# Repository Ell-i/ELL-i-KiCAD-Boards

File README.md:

# ELL-i-KiCAD-Boards
ELL-i's Public KiCAD Designs

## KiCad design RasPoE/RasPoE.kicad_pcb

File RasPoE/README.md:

#RasPoE user instructions
##Caution

Always disconnect cable between RasPoE and Rasberry Pi before connecting or disconnecting cable between RasPoE and PoE switch to avoid damage to your Raspberry Pi!

##Usage
Setting up RasPoE is simple: you need a Power over Ethernet (PoE) switch or injector to provide power to your Raspberry Pi. Mount RasPoE on top of your Raspberry Pi, connect RasPoE to PoE switch and finally connect RasPoE to Raspberry Pi. No special software is needed, start-up is automatic.

If you disconnect the RasPoE, always disconnect the cable to Raspberry Pi first! The PoE voltages can jump over transformer when cable is disconnected, disconnecting cable to Raspberry Pi prevents damage.

RasPoE uses only 5V and GND pins and it has tall header, which means you can stack Raspberry Pi HAT on top of it.
Specification

RasPoE is based on AG9805-M PoE DC/DC module which automatically negotiates the PoE power and provides 5V DC for Raspberry Pi.

While AG9805M can provide 1.8 A (9W) of power, current to Raspberry Pi is limited by 1.25 A self-resettible fuse. Please note the total current if you are using power-hungry USB peripherals

##Open Hardware
RasPoE is open source hardware, you can download the design files at ELL-i Open Source Co-operative's github-repository here. You can find out more about ELL-i at [ELL-i's website](http://ell-i.org).

##Hacking
RasPoE is made for hackers and makers. We cannot guess every possible application where RasPoE will be used so we have made things simple for some modifications.

###Raw PoE power
If your project needs unregulated high voltage, you can tap into RasPoE's "Raw PoE" pads. These pads expose the PoE voltage for your convenience, you can solder wires to them. Please note that any load on these pads will disrupt the PoE negotiation, so you must use relay controlled by Raspberry Pi to connect high voltage load only after the power has been setup. Do not add a lot of capacitance on these pins either to avoid inrush current tripping your PoE switch overcurrent protection.

###DC output pins
If you need to power some small external load, such as Arduino, you can add connector to the "DC OUT" pins. This output is not protected by fuse, so please be careful to not overload the AG9805 to avoid damage to your RasPoE.
Adjust

If you need to tune the output voltage a bit, you can solder a resistor to ADJUST pin as instructed in [AG9805-M datasheet](http://www.semiconductorstore.com/pages/asp/DownloadAttachment.asp?d=83464&e=i). Please be careful to not exceed your Raspberry Pi's maximum voltage.

###Other voltages

AG9803 and AG98012 modules provide 3.3 V and 12 V outputs respectively. You can desolder the AG9805 using hot air, disconnect the fuse F1 and solder a replacement module in if you want to! This is perfect for Raspberry Pi HATs which require 12V and provide 5V to RaspBerry Pi.

##Troubleshooting

If your Raspberry Pi does not power up or network connection fails, please check:

    Are you using a CAT5 or better Ethernet cable?
    Is the RasPoE properly connected?
    Does your switch support PoE technology?

If the problem remains, please contact us at support@ell-i.org and we'll help you with the issue. 

RasPoE emits high-pitched noise when there is  low load, this is normal. You can add optional load resistors R6, R7 to avoid this noise.

##How to buy
RasPoE is available through [Elecrow's webshop](http://www.elecrow.com/raspoeraspberry-pi-poe-shield-p-1479.html).

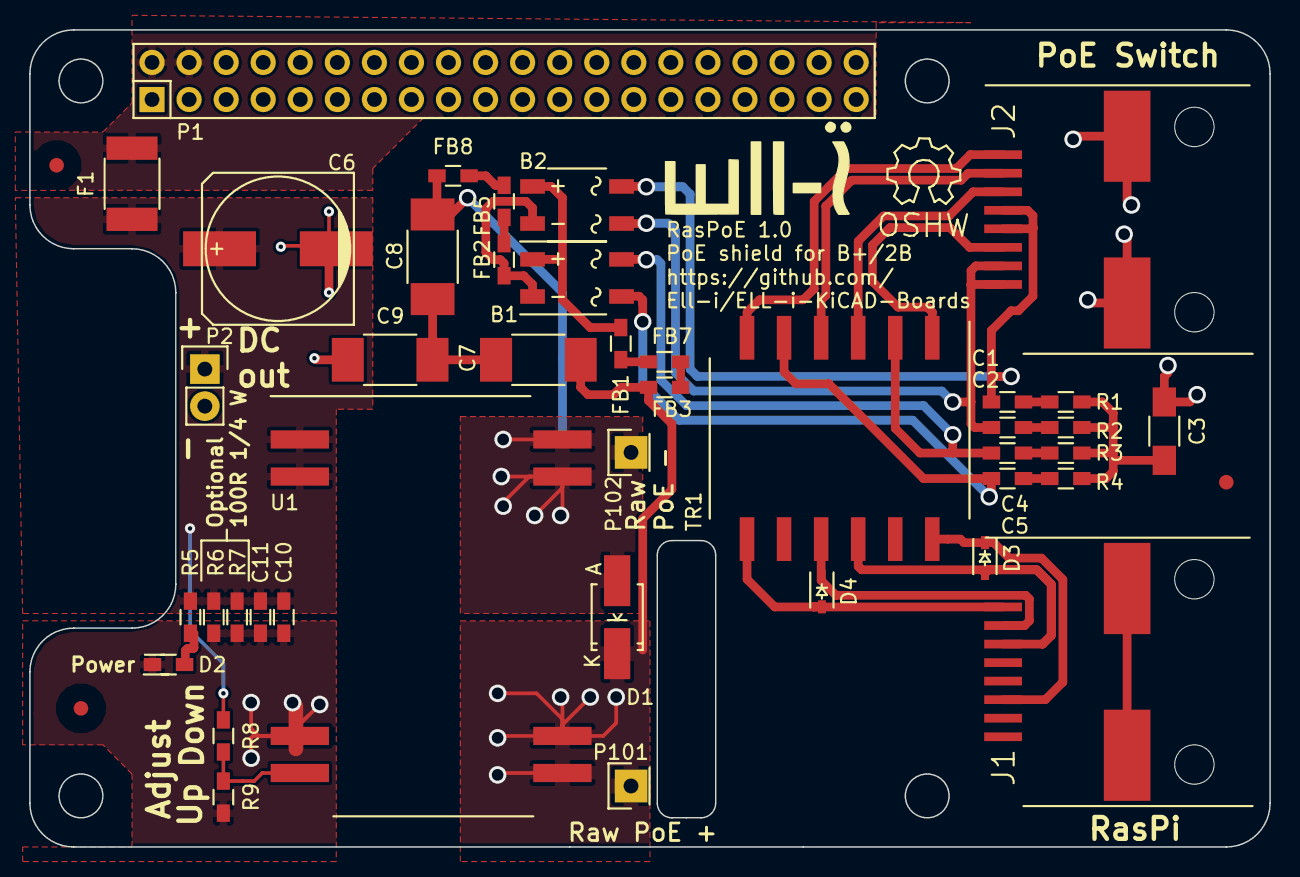
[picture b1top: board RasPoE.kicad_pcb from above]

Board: 2 copper layers, 85.0 x 56.0 mm, 46 parts (0 on the bottom side), 32 nets.

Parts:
B1, B2: MB110S; TO-269AA
C1, C2, C4, C5: 10n 100V; R_0603_HandSoldering
C3: 1n 2kV; C_1206_HandSoldering
C6: 470u; c_elec_10x10
C7, C8, C9: 4n7 2kV; C_1812_HandSoldering
C10: 100n; R_0603_HandSoldering
C11: 10u; R_0603_HandSoldering
D1: SMA58; Diode-SMA_Handsoldering
D2: LED; R_0603_HandSoldering
D3, D4: TVS; SOD-323
F1: PTC 1A25; R_1812
FB1, FB2, FB3, FB5, FB7, FB8: WE 742792651; R_0603_HandSoldering
FID1, FID2, FID3: 1, 2 mm; Fiducial_2mm_dia
J1: RJSSE-5080; RJSSE-5380
J2: RJSSE-5380
LOGO101: OPEN_HARDWARE_1; Symbol_OSHW-Logo_SilkScreen
LOGO102: ELL-i; ELL-i_large
P1: CONN_02X20; Pin_Header_Straight_2x20
P2: Screw terminal 2.54mm; Pin_Header_Straight_1x02
P101, P102: Wire pad; Pin_Header_Straight_1x01
R1, R2, R3, R4: 75R; R_0603_HandSoldering
R5: 180R; R_0603_HandSoldering
R6, R7: 100R 250 mW; R_0603_HandSoldering
R8, R9: R; R_0603_HandSoldering
TR1: WE_749012011
U1: AG9805-MT; AG9800

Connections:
+5V: F1.2, P1.2, P1.4
/ADJ: R8.2, R9.1, U1.4
/AG_IN_+: C7.1, D1.1, FB7.2, P101.1, U1.5, U1.6
/AG_IN_-: C8.1, D1.2, FB8.2, P102.1, U1.7, U1.8
/AG_OUT_+: C6.1, C10.1, C11.1, F1.1, P2.1, R5.1, R6.1, R7.1, R8.1, U1.1, U1.2
/POE_A+: B1.4, C4.1, TR1.2
/POE_A-: B1.2, C5.1, TR1.5
/POE_B+: B2.2, C2.1, J2.7, J2.8
/POE_B-: B2.4, C1.1, J2.4, J2.5
/RD+: D3.2, J1.3, TR1.10
/RD-: D3.1, J1.6, TR1.12
/RX+: J2.3, TR1.3
/RX-: J2.6, TR1.1
/TD+: D4.2, J1.1, TR1.7
/TD-: D4.1, J1.2, TR1.9
/TX+: J2.1, TR1.6
/TX-: J2.2, TR1.4
/VIN: B1.3, B2.3, FB1.1
GND: C6.2, C9.1, C10.2, C11.2, D2.1, P1.6, P1.9, P1.14, P1.20, P1.25, P1.30, P1.34, P1.39, P2.2, R6.2, R7.2, R9.2, U1.3
GNDA: C3.2, J2.9
GNDD: B1.1, B2.1, FB2.1
unnamed: C1.2, R1.1
unnamed: C2.2, R2.1
unnamed: C3.1, R1.2, R2.2, R3.2, R4.2
unnamed: C4.2, R3.1
unnamed: C5.2, R4.1
unnamed: C7.2, C8.2, C9.2
unnamed: D2.2, R5.2
unnamed: FB1.2, FB3.1
unnamed: FB2.2, FB5.1
unnamed: FB3.2, FB7.1
unnamed: FB5.2, FB8.1

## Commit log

2015-06-22 Add git ignore file
2015-06-22 Add RasPoE files
2015-06-22 Cosmetic touchups
2015-06-22 Add printouts
2015-11-11 Cleanup schematic
2015-11-11 Add Revision information to schematic and layout
2015-11-11 Add footprints
2015-11-11 Add AG9800 library file
2015-11-11 Add BoM
2015-11-11 Add exported AG9800 to libraries used by project
2015-11-11 Add local exported footprints to FP-LIB-TABLE
2015-11-11 Export missing library files
2015-11-11 Remove redundant .dcm file
2015-11-11 Add user instructions to README
2015-11-11 Fix typo in support email address
2016-02-29 Add arduino source files
2016-02-29 Add description
2016-02-29 Add license, schematic, keywords, example program
2016-03-02 Adde tsys01 3d render images.
2016-03-02 Fixed images.
2016-03-02 Image fix 2
2016-03-02 Image fix 3
2016-03-02 Image fix 4
2016-03-02 Added pin out explanation.
2016-03-02 Bugfix to pin out.
2016-03-02 Bugfix 2 to pinout
2016-03-02 Fixed README syntax
2016-03-02 Fixed typo in README
2016-03-03 Added user instructions and an explanation of the R5 removal hack.
2016-03-03 Fixed typos and added text about the sensor island cut of hack.
2016-03-03 Fixed a typo and adda a sentence.
2016-03-03 Fixed typos
2016-03-05 Added instructions for debugging problems with the temperature sensor board.
2016-03-05 Fixed typos on the Troubleshooting chapter.
2016-03-05 Fixed a type in tsys01 readme.
2016-03-05 FIxed anuther type in tsys01 readme.
2016-03-06 Add mechanical dimensions, mounting instructions
2016-03-06 Add link to test video
2016-03-06 Fix readme video link formatting
2016-03-06 Add kicad libraries
2016-03-06 Remove kicad libraries from gitignore, add kicad .dcm files to gitignore
2016-03-06 separate kicad libraries from rest of the work to comply with LGPL2
2016-03-17 Changed library to use 24 bit ADC values of sensor.
2016-03-17 Fixed debug instruction to one that works.
2016-03-17 Changed debug flag to be off by default.
2016-03-17 Fixed typo and made instruction clearer.
2016-03-24 Add link to webshop
2016-03-24 Fix typo in README
2016-05-23 Update README of tsys01 with a new link
2016-10-29 add draft files
2020-07-31 Set chip select pind mode on Tsys01 creation
